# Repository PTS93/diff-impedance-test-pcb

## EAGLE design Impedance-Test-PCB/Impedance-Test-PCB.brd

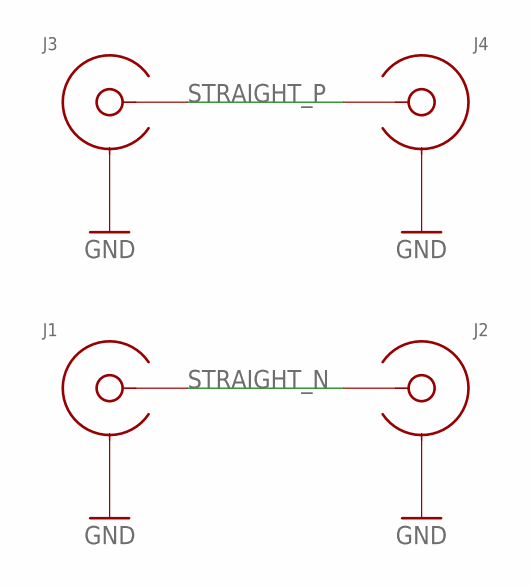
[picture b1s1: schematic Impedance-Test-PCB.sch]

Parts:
J1, J2, J3, J4: SMA-EDGE-LAUNCH4020N4; SMA-EDGE-LAUNCH-4L-4020-N4

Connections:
GND: J1.BOTTOM_GND (SHIELD), J1.GND@1 (SHIELD), J1.GND@2 (SHIELD), J1.GND@3 (SHIELD), J1.GND@4 (SHIELD), J1.GND@5 (SHIELD), J1.GND@6 (SHIELD), J1.GND@7 (SHIELD), J1.GND@8 (SHIELD), J1.GND@9 (SHIELD), J1.GND@10 (SHIELD), J1.GND@14 (SHIELD), J1.GND@15 (SHIELD), J1.GND@16 (SHIELD), J1.GND@17 (SHIELD), J1.GND_PAD1 (SHIELD), J1.GND_PAD2 (SHIELD), J1.P$1 (SHIELD), J1.P$2 (SHIELD), J1.P$3 (SHIELD), J1.P$4 (SHIELD), J1.P$5 (SHIELD), J2.BOTTOM_GND (SHIELD), J2.GND@1 (SHIELD), J2.GND@2 (SHIELD), J2.GND@3 (SHIELD), J2.GND@4 (SHIELD), J2.GND@5 (SHIELD), J2.GND@6 (SHIELD), J2.GND@7 (SHIELD), J2.GND@8 (SHIELD), J2.GND@9 (SHIELD), J2.GND@10 (SHIELD), J2.GND@14 (SHIELD), J2.GND@15 (SHIELD), J2.GND@16 (SHIELD), J2.GND@17 (SHIELD), J2.GND_PAD1 (SHIELD), J2.GND_PAD2 (SHIELD), J2.P$1 (SHIELD), J2.P$2 (SHIELD), J2.P$3 (SHIELD), J2.P$4 (SHIELD), J2.P$5 (SHIELD), J3.BOTTOM_GND (SHIELD), J3.GND@1 (SHIELD), J3.GND@2 (SHIELD), J3.GND@3 (SHIELD), J3.GND@4 (SHIELD), J3.GND@5 (SHIELD), J3.GND@6 (SHIELD), J3.GND@7 (SHIELD), J3.GND@8 (SHIELD), J3.GND@9 (SHIELD), J3.GND@10 (SHIELD), J3.GND@14 (SHIELD), J3.GND@15 (SHIELD), J3.GND@16 (SHIELD), J3.GND@17 (SHIELD), J3.GND_PAD1 (SHIELD), J3.GND_PAD2 (SHIELD), J3.P$1 (SHIELD), J3.P$2 (SHIELD), J3.P$3 (SHIELD), J3.P$4 (SHIELD), J3.P$5 (SHIELD), J4.BOTTOM_GND (SHIELD), J4.GND@1 (SHIELD), J4.GND@2 (SHIELD), J4.GND@3 (SHIELD), J4.GND@4 (SHIELD), J4.GND@5 (SHIELD), J4.GND@6 (SHIELD), J4.GND@7 (SHIELD), J4.GND@8 (SHIELD), J4.GND@9 (SHIELD), J4.GND@10 (SHIELD), J4.GND@14 (SHIELD), J4.GND@15 (SHIELD), J4.GND@16 (SHIELD), J4.GND@17 (SHIELD), J4.GND_PAD1 (SHIELD), J4.GND_PAD2 (SHIELD), J4.P$1 (SHIELD), J4.P$2 (SHIELD), J4.P$3 (SHIELD), J4.P$4 (SHIELD), J4.P$5 (SHIELD)
STRAIGHT_N: J1.CENTER@1 (CENTER), J1.CENTER@2 (CENTER), J2.CENTER@1 (CENTER), J2.CENTER@2 (CENTER)
STRAIGHT_P: J3.CENTER@1 (CENTER), J3.CENTER@2 (CENTER), J4.CENTER@1 (CENTER), J4.CENTER@2 (CENTER)

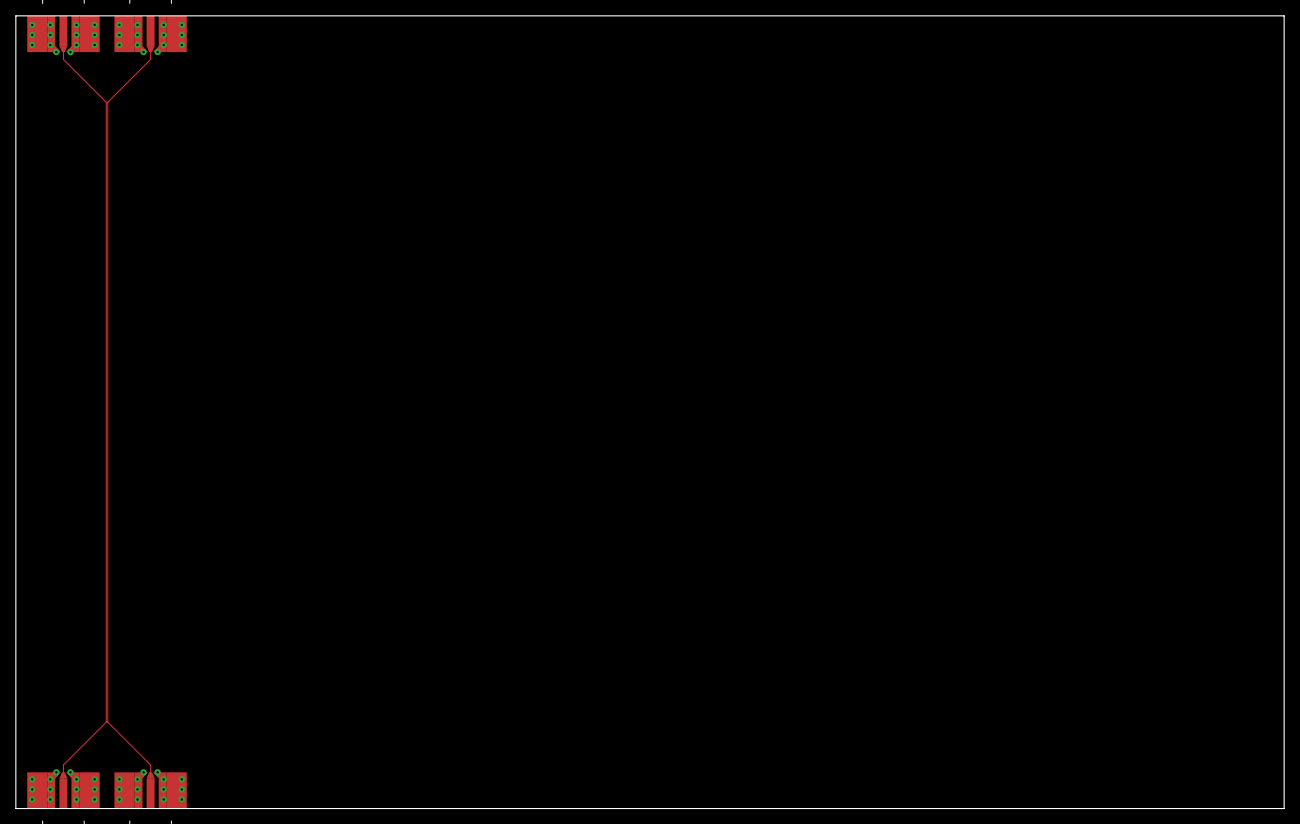
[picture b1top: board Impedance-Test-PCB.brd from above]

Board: 4 copper layers, 160.0 x 100.0 mm, 4 parts (0 on the bottom side), 3 nets.

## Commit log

2019-10-25 added intial SMA component to library
2019-10-25 Added PCB with first test pair
2019-10-25 removed thermals from sma footprint pads
